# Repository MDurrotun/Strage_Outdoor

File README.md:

# Strage_Outdoor

Strage is a device used by people to find other people who have strage devices.

Specification :
- Arduino Nano
- IMU GY-25
- XBee Pro S2
- Bluetooth V4 - HM 11

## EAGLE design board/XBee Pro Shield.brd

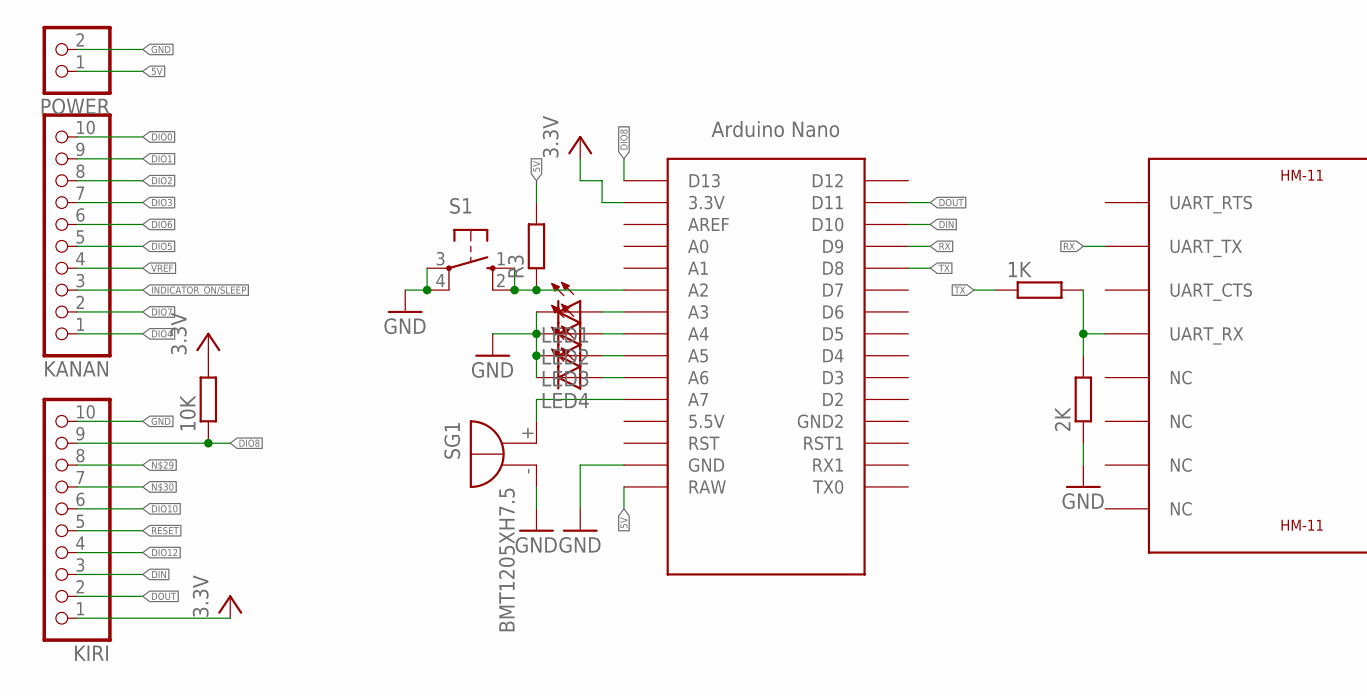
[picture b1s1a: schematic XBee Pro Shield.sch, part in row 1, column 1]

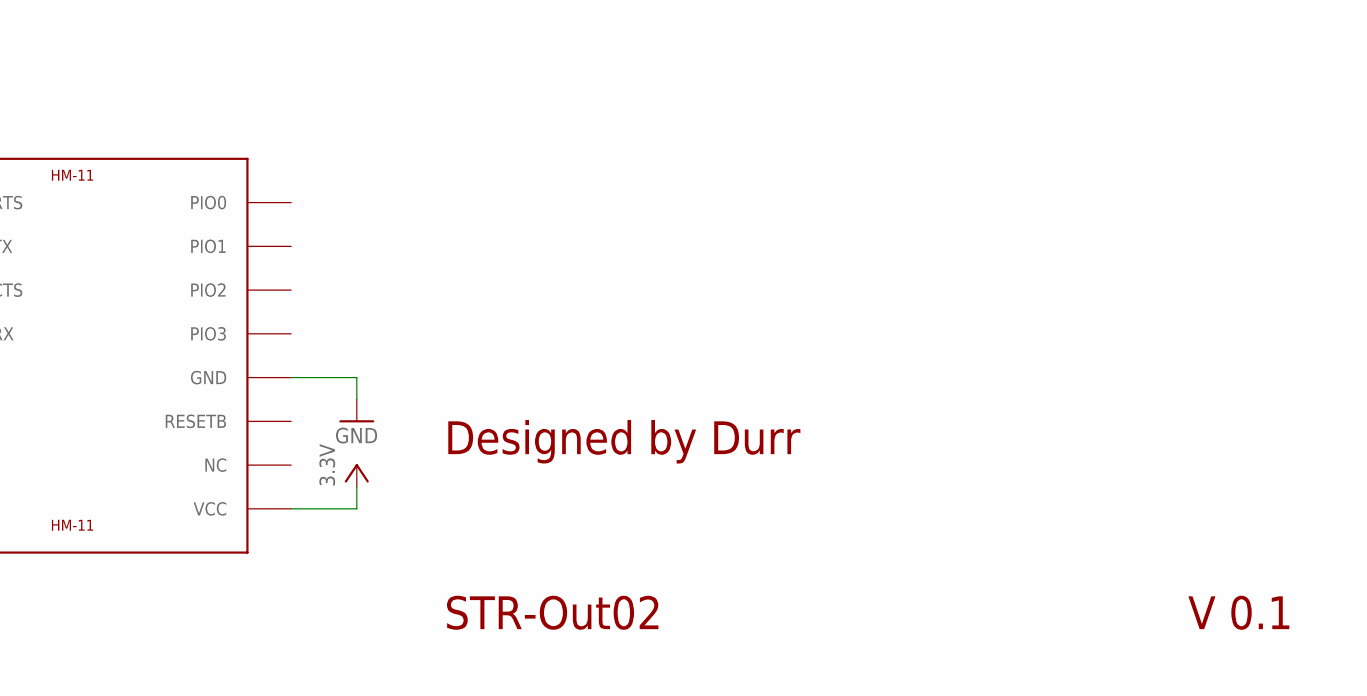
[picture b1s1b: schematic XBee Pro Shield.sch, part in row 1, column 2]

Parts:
1K, 2K, 10K: R-EU_R1206; R1206
KANAN: PINHD-1X10; 1X10
KIRI: PINHD-1X10; 1X10
LED1, LED2, LED3, LED4: LED5MM
POWER: PINHD-1X2; 1X02
R3: R-EU_R1206; R1206
S1: 40-XX; B3F-40XX
SG1: BMT1205XH7.5
U$1: HM-11
U$2: NANO

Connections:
5V: POWER.1, R3.2, U$2.RAW
DIN: KIRI.3, U$2.D10
DIO0: KANAN.10
DIO1: KANAN.9
DIO2: KANAN.8
DIO3: KANAN.7
DIO4: KANAN.1
DIO5: KANAN.5
DIO6: KANAN.6
DIO7: KANAN.2
DIO8: 10K.1, KIRI.9, U$2.D13
DIO10: KIRI.6
DIO12: KIRI.4
DOUT: KIRI.2, U$2.D11
GND: 2K.1, KIRI.10, LED1.K (C), LED2.K (C), LED3.K (C), LED4.K (C), POWER.2, S1.3, S1.4 (P1), SG1.-, U$1.GND, U$2.GND
INDICATOR_ON/SLEEP: KANAN.3
unnamed: SG1.+, U$2.A7
unnamed: 1K.2, 2K.2, U$1.UART_RX
unnamed: LED1.A, U$2.A3
unnamed: R3.1, S1.1 (S), S1.2 (S1), U$2.A2
unnamed: LED4.A, U$2.A6
unnamed: LED3.A, U$2.A5
unnamed: LED2.A, U$2.A4
RESET: KIRI.5
RX: U$1.UART_TX, U$2.D9
TX: 1K.1, U$2.D8
VCC: 10K.2, KIRI.1, U$1.VCC, U$2.3.3V
VREF: KANAN.4

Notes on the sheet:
Designed by Durr
STR-Out02
V 0.1

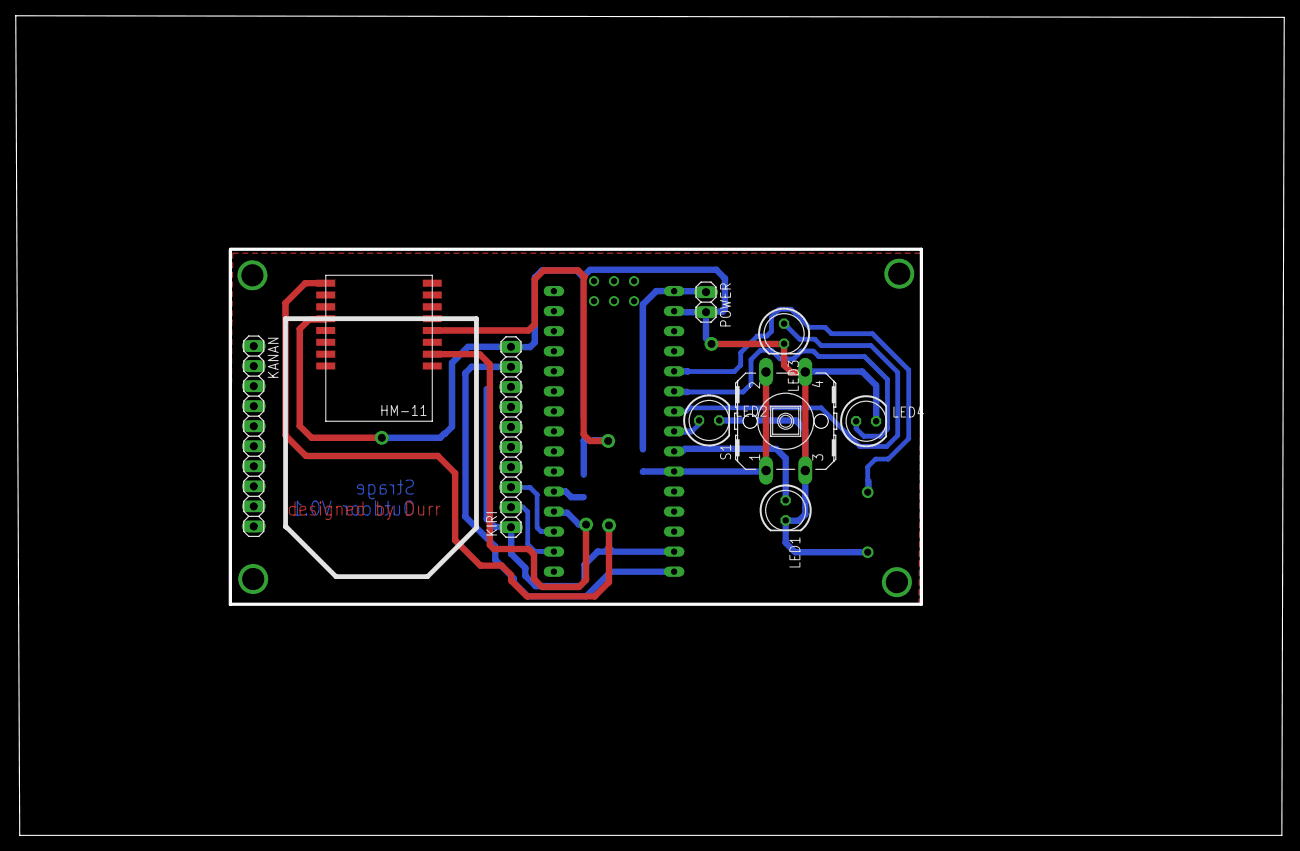
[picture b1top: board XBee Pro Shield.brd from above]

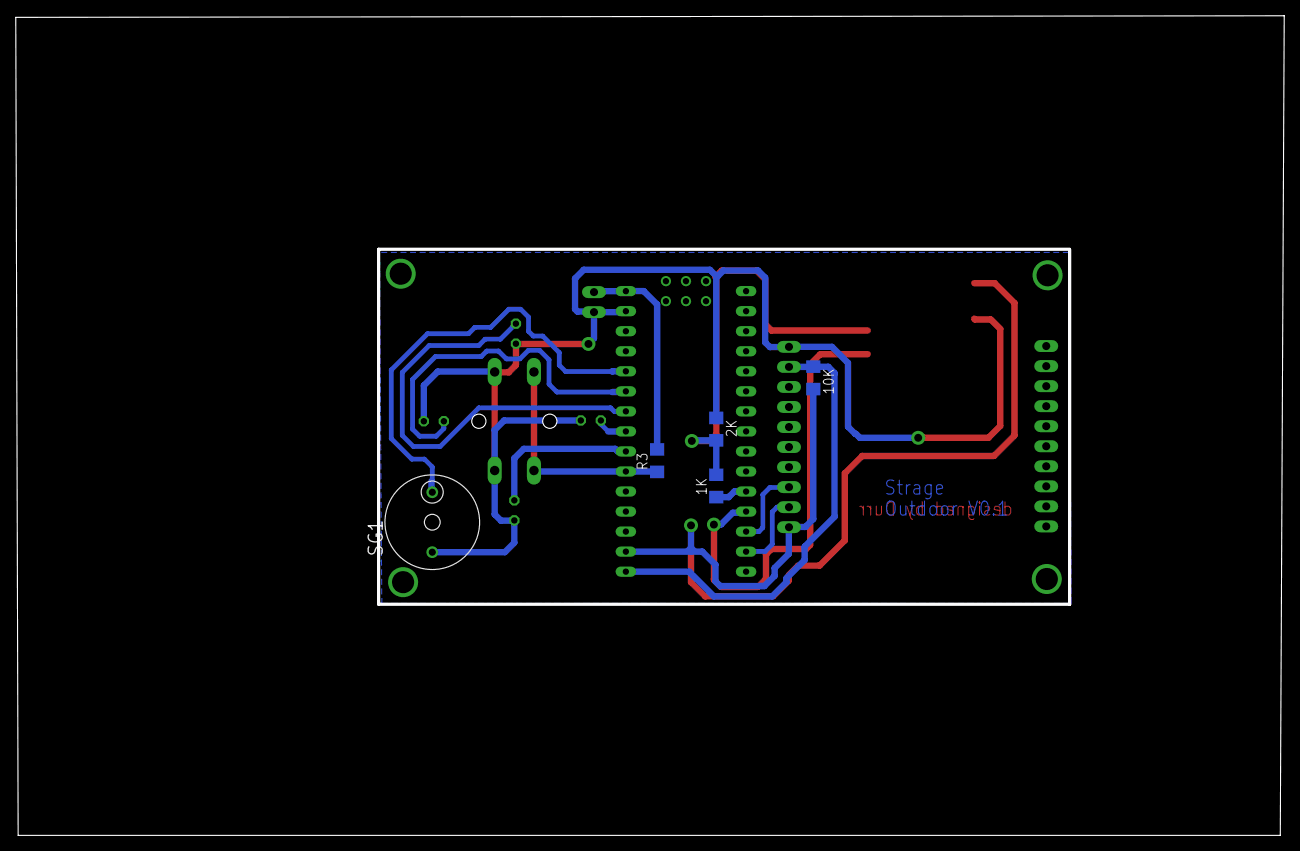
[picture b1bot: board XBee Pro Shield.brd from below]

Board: 2 copper layers, 160.8 x 103.9 mm, 15 parts (5 on the bottom side), 15 nets.

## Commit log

2019-01-01 Main Program and Schematics
